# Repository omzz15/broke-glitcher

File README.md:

# Glitch Penguin 🐧
> **Glitch Penguin is a low cost all in one platform for fault injection and side channel attacks.**

There are many great glitching products out there (see [NewAE](https://www.newae.com/), [PicoGlitcher](https://fault-injection-library.readthedocs.io/en/latest/overview/)) but their cost can make the barrier to entry high especially for a large group environment such as a classroom. Glitch Penguin is a cost optimized glitching platform with a target price of only $10 a board. (We are currently at ~$16 per board using JLCPCB for board manufactuaring and assembly plus US tariffs)

## Highlights
- Powered by the [RP2040](https://www.raspberrypi.com/products/rp2040/)
- Fully open-source hardware and firmware
- Integrated analog frontend
  - 10-bit 35 MS/s ADC
  - AC coupled input range of +/-50mV
  - Bandwidth of 5 MHz
- SMA connectors for differnatial sense and glitch output
- Integrated [MSPMOG3507](https://www.ti.com/product/MSPM0G3507) target

## Overview
At the core of the board sits the RP2040 which handles

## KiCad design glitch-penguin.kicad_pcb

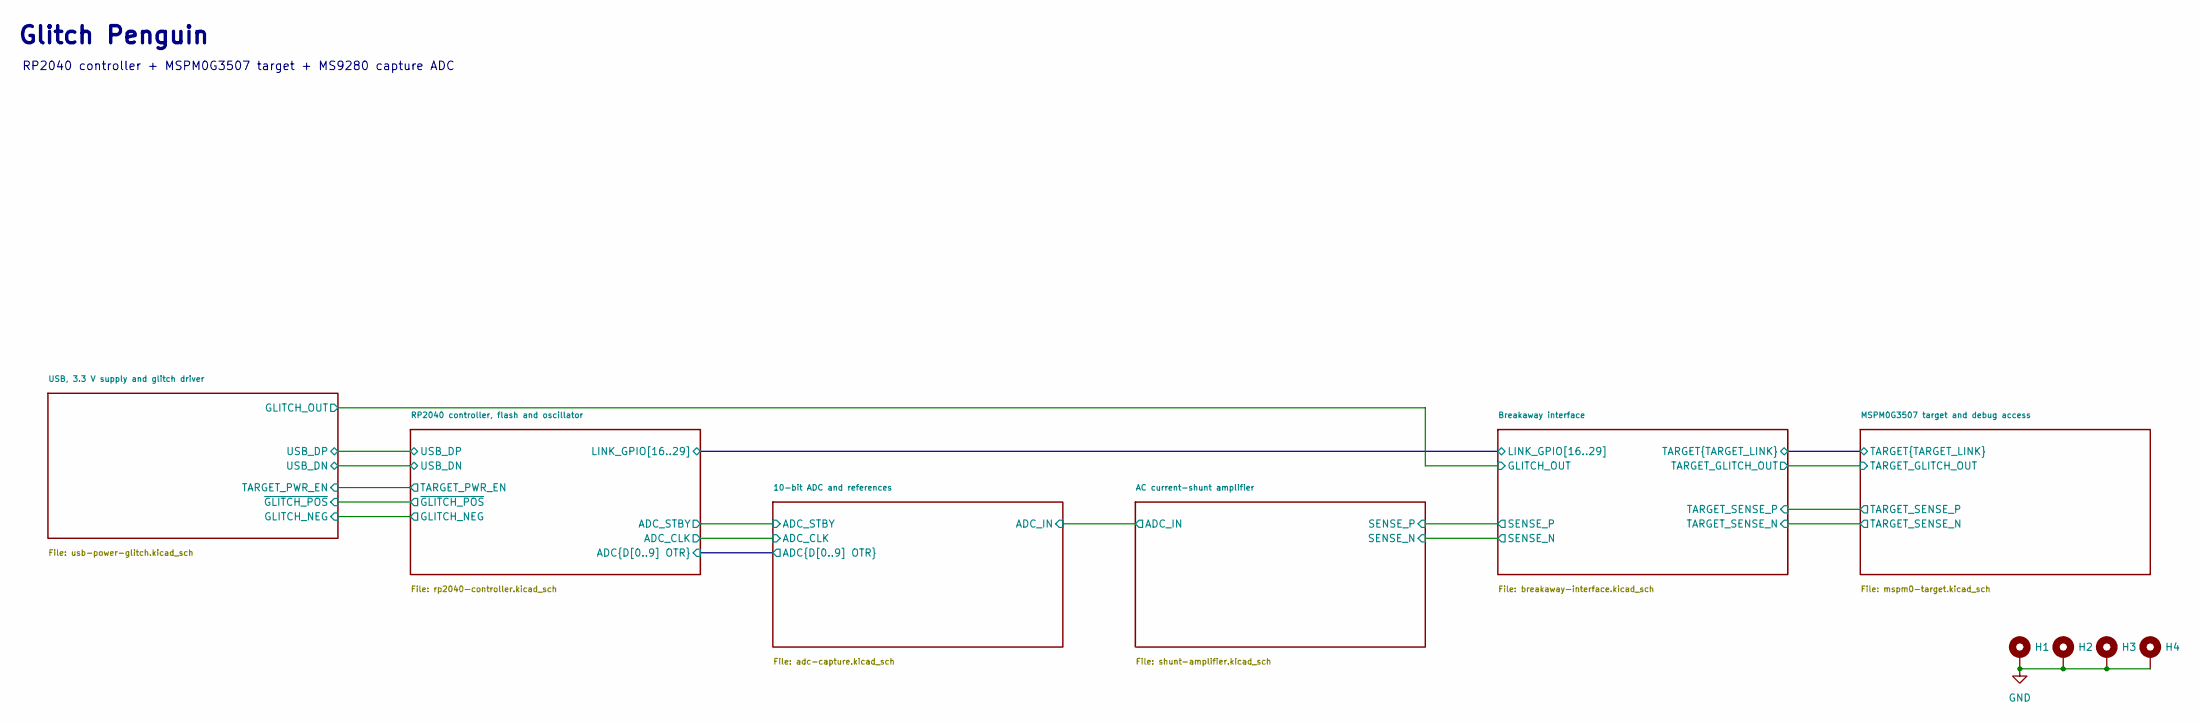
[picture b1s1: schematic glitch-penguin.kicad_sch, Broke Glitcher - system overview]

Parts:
H1, H2, H3, H4: MountingHole_Pad; MountingHole_2.2mm_M2_Pad

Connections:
GND: H1.1 (1_1), H2.1 (1_1), H3.1 (1_1), H4.1 (1_1); also elsewhere on the board

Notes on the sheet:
Glitch Penguin
RP2040 controller + MSPM0G3507 target + MS9280 capture ADC

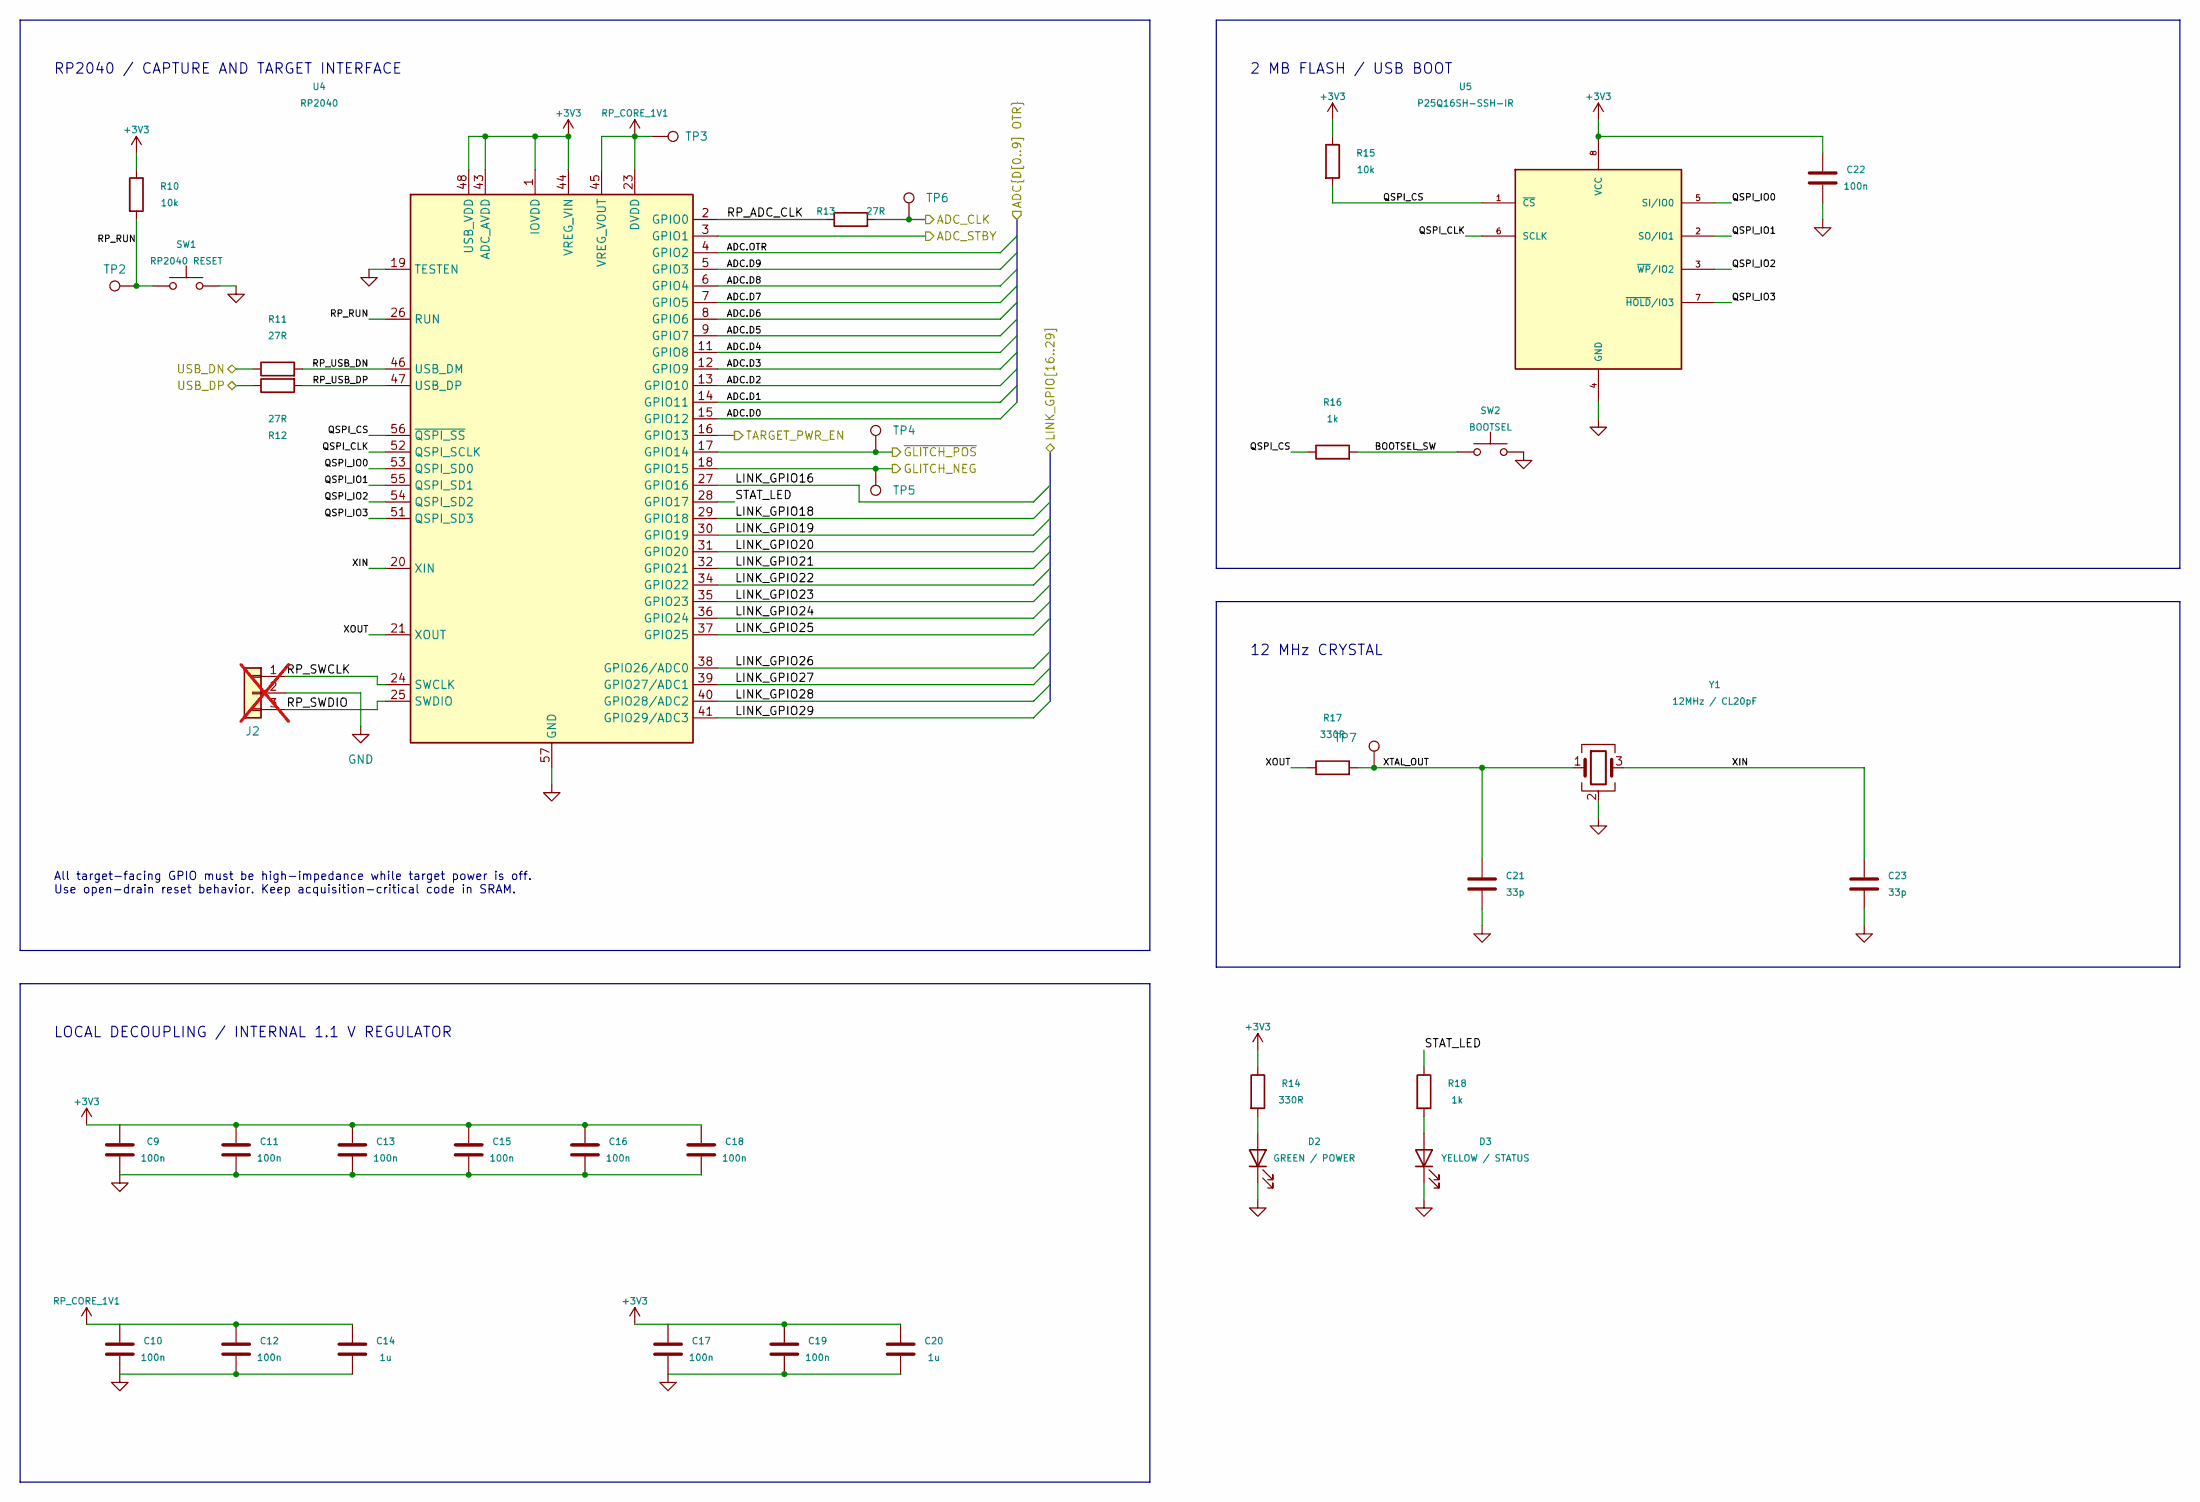
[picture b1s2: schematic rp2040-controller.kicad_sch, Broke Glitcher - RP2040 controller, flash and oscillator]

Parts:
C9, C10, C11, C12, C13, C15, C16, C17, C18, C19, C22: 100n; C_0402_1005Metric; Tolerance ±10%; Voltage Rating 16 V; MPN CL05B104KO5NNNC; LCSC Part # C1525
C14, C20: 1u; C_0603_1608Metric; MPN CL10A105KB8NNNC; LCSC Part # C15849
C21, C23: 33p; C_0402_1005Metric; Tolerance ±5%; Voltage Rating 50 V; MPN 0402CG330J500NT; LCSC Part # C1562
D2: GREEN / POWER; LED_0603_1608Metric; MPN KT-0603G; LCSC Part # C12624
D3: YELLOW / STATUS; LED_0603_1608Metric; MPN KT-0603Y; LCSC Part # C2287
J2: Conn_01x03; PinHeader_1x03_P2.54mm_Vertical; not fitted
R10, R15: 10k; R_0402_1005Metric; Tolerance ±1%; Voltage Rating 50 V; MPN 0402WGF1002TCE; LCSC Part # C25744
R11, R12, R13: 27R; R_0402_1005Metric; Tolerance ±1%; Voltage Rating 50 V; MPN 0402WGF270JTCE; LCSC Part # C25100
R14, R17: 330R; R_0402_1005Metric; Tolerance ±1%; Voltage Rating 50 V; MPN 0402WGF3300TCE; LCSC Part # C25104
R16, R18: 1k; R_0402_1005Metric; Tolerance ±1%; Voltage Rating 50 V; MPN 0402WGF1001TCE; LCSC Part # C11702
SW1: RP2040 RESET; SW_SPST_TS-1088-xR020; MPN TS-1088-AR02016; LCSC Part # C720477
SW2: BOOTSEL; SW_SPST_TS-1088-xR020; MPN TS-1088-AR02016; LCSC Part # C720477
TP2, TP3, TP4, TP5, TP6: TestPoint; TestPoint_Pad_D1.0mm
TP7: XOUT; TestPoint_Pad_D1.0mm
U4: RP2040; QFN-56-1EP_7x7mm_P0.4mm_EP3.2x3.2mm; MPN RP2040; LCSC Part # C2040
U5: P25Q16SH-SSH-IR; SOIC-8_3.9x4.9mm_P1.27mm; MPN P25Q16SH-SSH-IR; LCSC Part # C7466814
Y1: 12MHz / CL20pF; Crystal_SMD_3225-4Pin_3.2x2.5mm; MPN X322512MSB4SI; LCSC Part # C9002

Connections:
+3V3: C9.1, C11.1, C13.1, C15.1, C16.1, C17.1, C18.1, C19.1, C20.1, C22.1, R10.1, R14.1, R15.1, U4.1 (IOVDD), U4.10 (IOVDD), U4.22 (IOVDD), U4.33 (IOVDD), U4.42 (IOVDD), U4.43 (ADC_AVDD), U4.44 (VREG_VIN), U4.48 (USB_VDD), U4.49 (IOVDD), U5.8 (VCC); also elsewhere on the board
/10-bit ADC and references/ADC.D0: U4.15 (GPIO12); also elsewhere on the board
/10-bit ADC and references/ADC.D1: U4.14 (GPIO11); also elsewhere on the board
/10-bit ADC and references/ADC.D2: U4.13 (GPIO10); also elsewhere on the board
/10-bit ADC and references/ADC.D3: U4.12 (GPIO9); also elsewhere on the board
/10-bit ADC and references/ADC.D4: U4.11 (GPIO8); also elsewhere on the board
/10-bit ADC and references/ADC.D5: U4.9 (GPIO7); also elsewhere on the board
/10-bit ADC and references/ADC.D6: U4.8 (GPIO6); also elsewhere on the board
/10-bit ADC and references/ADC.D7: U4.7 (GPIO5); also elsewhere on the board
/10-bit ADC and references/ADC.D8: U4.6 (GPIO4); also elsewhere on the board
/10-bit ADC and references/ADC.D9: U4.5 (GPIO3); also elsewhere on the board
/10-bit ADC and references/ADC.OTR: U4.4 (GPIO2); also elsewhere on the board
/10-bit ADC and references/ADC_CLK: R13.2, TP6.1 (1_1); also elsewhere on the board
/10-bit ADC and references/ADC_STBY: U4.3 (GPIO1); also elsewhere on the board
/Breakaway interface/LINK_GPIO16: U4.27 (GPIO16); also elsewhere on the board
/Breakaway interface/LINK_GPIO18: U4.29 (GPIO18); also elsewhere on the board
/Breakaway interface/LINK_GPIO19: U4.30 (GPIO19); also elsewhere on the board
/Breakaway interface/LINK_GPIO20: U4.31 (GPIO20); also elsewhere on the board
/Breakaway interface/LINK_GPIO21: U4.32 (GPIO21); also elsewhere on the board
/Breakaway interface/LINK_GPIO22: U4.34 (GPIO22); also elsewhere on the board
/Breakaway interface/LINK_GPIO23: U4.35 (GPIO23); also elsewhere on the board
/Breakaway interface/LINK_GPIO24: U4.36 (GPIO24); also elsewhere on the board
/Breakaway interface/LINK_GPIO25: U4.37 (GPIO25); also elsewhere on the board
/Breakaway interface/LINK_GPIO26: U4.38 (GPIO26/ADC0); also elsewhere on the board
/Breakaway interface/LINK_GPIO27: U4.39 (GPIO27/ADC1); also elsewhere on the board
/Breakaway interface/LINK_GPIO28: U4.40 (GPIO28/ADC2); also elsewhere on the board
/Breakaway interface/LINK_GPIO29: U4.41 (GPIO29/ADC3); also elsewhere on the board
/RP2040 controller, flash and oscillator/BOOTSEL_SW: R16.2, SW2.1
/RP2040 controller, flash and oscillator/GLITCH_NEG: TP5.1 (1_1), U4.18 (GPIO15); also elsewhere on the board
/RP2040 controller, flash and oscillator/QSPI_CLK: U4.52 (QSPI_SCLK), U5.6 (SCLK)
/RP2040 controller, flash and oscillator/QSPI_CS: R15.2, R16.1, U4.56 (~QSPI_SS), U5.1 (~CS)
/RP2040 controller, flash and oscillator/QSPI_IO0: U4.53 (QSPI_SD0), U5.5 (SI/IO0)
/RP2040 controller, flash and oscillator/QSPI_IO1: U4.55 (QSPI_SD1), U5.2 (SO/IO1)
/RP2040 controller, flash and oscillator/QSPI_IO2: U4.54 (QSPI_SD2), U5.3 (~WP/IO2)
/RP2040 controller, flash and oscillator/QSPI_IO3: U4.51 (QSPI_SD3), U5.7 (~HOLD/IO3)
/RP2040 controller, flash and oscillator/RP_ADC_CLK: R13.1, U4.2 (GPIO0)
/RP2040 controller, flash and oscillator/RP_RUN: R10.2, SW1.1, TP2.1 (1_1), U4.26 (RUN)
/RP2040 controller, flash and oscillator/RP_SWCLK: J2.1, U4.24 (SWCLK)
/RP2040 controller, flash and oscillator/RP_SWDIO: J2.3, U4.25 (SWDIO)
/RP2040 controller, flash and oscillator/RP_USB_DN: R11.2, U4.46 (USB_DM)
/RP2040 controller, flash and oscillator/RP_USB_DP: R12.2, U4.47 (USB_DP)
/RP2040 controller, flash and oscillator/STAT_LED: R18.1, U4.28 (GPIO17)
/RP2040 controller, flash and oscillator/TARGET_PWR_EN: U4.16 (GPIO13); also elsewhere on the board
/RP2040 controller, flash and oscillator/USB_DN: R11.1; also elsewhere on the board
/RP2040 controller, flash and oscillator/USB_DP: R12.1; also elsewhere on the board
/RP2040 controller, flash and oscillator/XIN: C23.1, U4.20 (XIN), Y1.3
/RP2040 controller, flash and oscillator/XOUT: R17.1, U4.21 (XOUT)
/RP2040 controller, flash and oscillator/XTAL_OUT: C21.1, R17.2, TP7.1 (1_1), Y1.1
/RP2040 controller, flash and oscillator/~GLITCH_POS: TP4.1 (1_1), U4.17 (GPIO14); also elsewhere on the board
GND: C9.2, C10.2, C11.2, C12.2, C13.2, C14.2, C15.2, C16.2, C17.2, C18.2, C19.2, C20.2, C21.2, C22.2, C23.2, D2.1 (K), D3.1 (K), J2.2, SW1.2, SW2.2, U4.19 (TESTEN), U4.57 (GND), U5.4 (GND), Y1.2 (G), Y1.4 (G); also elsewhere on the board
unnamed: D2.2 (A), R14.2
unnamed: D3.2 (A), R18.2
RP_CORE_1V1: C10.1, C12.1, C14.1, TP3.1 (1_1), U4.23 (DVDD), U4.45 (VREG_VOUT), U4.50 (DVDD)

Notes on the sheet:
All target-facing GPIO must be high-impedance while target power is off. Use open-drain reset behavior. Keep acquisition-critical code in SRAM.
12 MHz CRYSTAL
LOCAL DECOUPLING / INTERNAL 1.1 V REGULATOR
RP2040 / CAPTURE AND TARGET INTERFACE
2 MB FLASH / USB BOOT

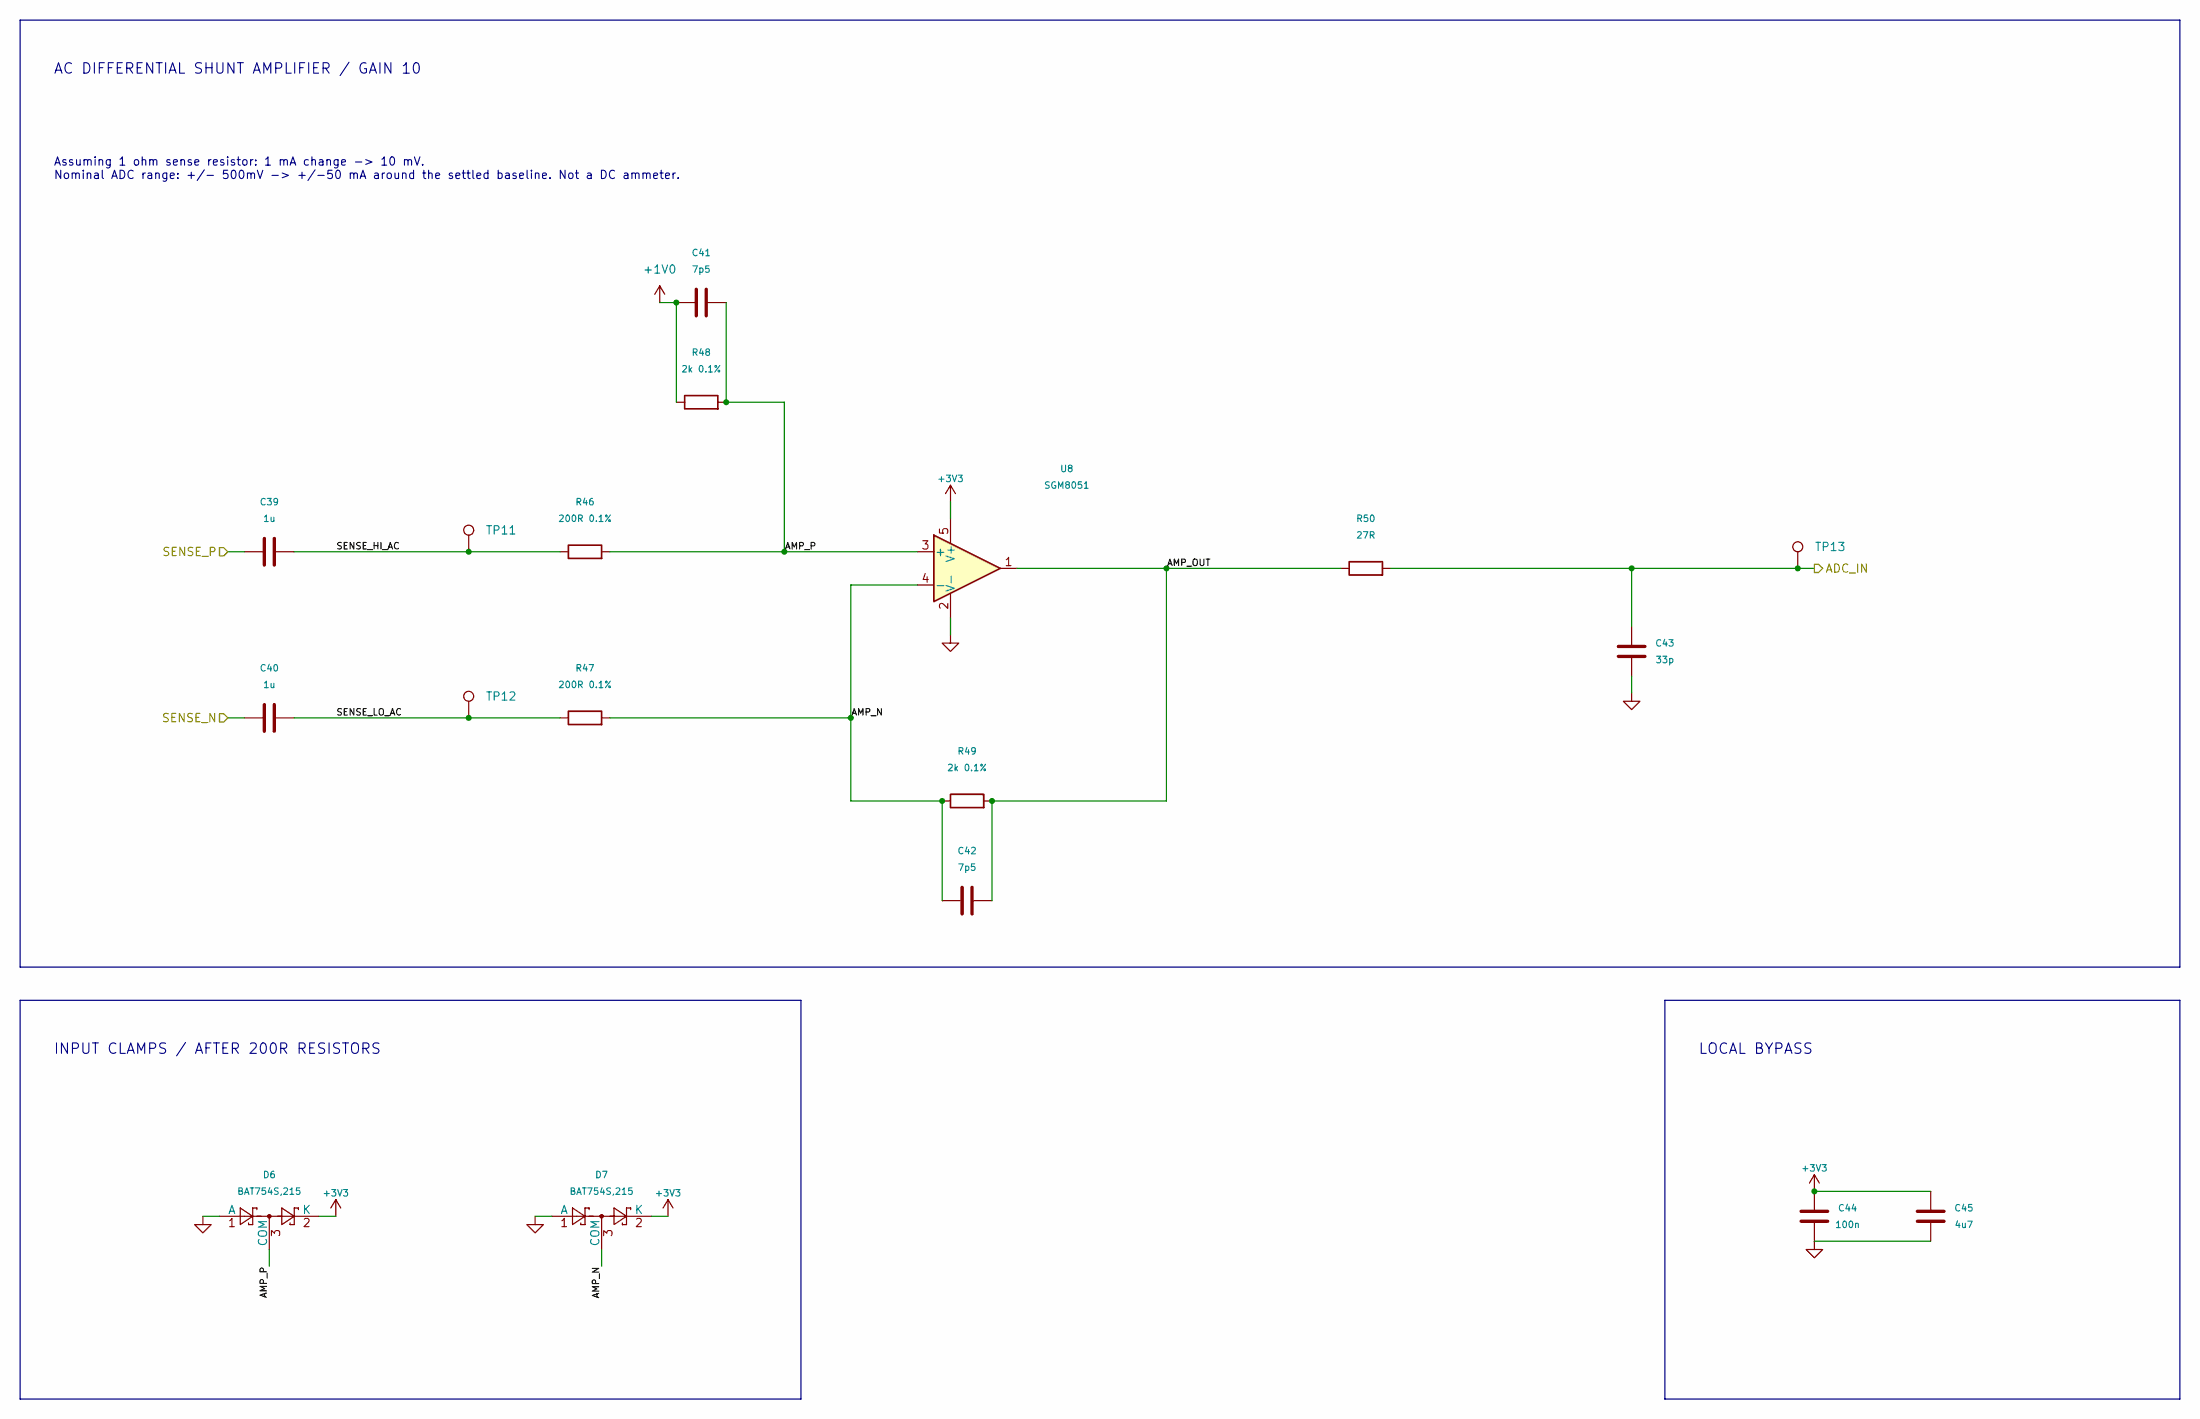
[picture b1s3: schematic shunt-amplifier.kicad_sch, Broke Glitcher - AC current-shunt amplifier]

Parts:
C39, C40: 1u; C_0603_1608Metric; MPN CL10A105KB8NNNC; LCSC Part # C15849
C41, C42: 7p5; C_0402_1005Metric; Tolerance ±0.25 pF; Voltage Rating 50 V; MPN 0402CG7R5C500NT; LCSC Part # C43514
C43: 33p; C_0402_1005Metric; Tolerance ±5%; Voltage Rating 50 V; MPN 0402CG330J500NT; LCSC Part # C1562
C44: 100n; C_0402_1005Metric; Tolerance ±10%; Voltage Rating 16 V; MPN CL05B104KO5NNNC; LCSC Part # C1525
C45: 4u7; C_0603_1608Metric; MPN CL10A475KP8NNNC; LCSC Part # C1705
D6, D7: BAT754S,215; SOT-23; MPN BAT754S,215; LCSC Part # C426771
R46, R47: 200R 0.1%; R_0603_1608Metric; MPN TC0325B2000T5F; LCSC Part # C2989022
R48, R49: 2k 0.1%; R_0402_1005Metric; Tolerance ±0.1%; Voltage Rating 50 V; MPN RT0402BRD072KL; LCSC Part # C852711
R50: 27R; R_0402_1005Metric; Tolerance ±1%; Voltage Rating 50 V; MPN 0402WGF270JTCE; LCSC Part # C25100
TP11, TP12, TP13: TestPoint; TestPoint_Pad_D1.0mm
U8: SGM8051; SOT-23-5; MPN SGM8051XN5/TR; LCSC Part # C5122371

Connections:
+1V0: C41.1, R48.1; also elsewhere on the board
+3V3: C44.1, C45.1, D6.2 (K), D7.2 (K), U8.5 (V+); also elsewhere on the board
/10-bit ADC and references/ADC_IN: C43.1, R50.2, TP13.1 (1_1); also elsewhere on the board
/AC current-shunt amplifier/AMP_N: C42.1, D7.3 (COM), R47.2, R49.1, U8.4 (-)
/AC current-shunt amplifier/AMP_OUT: C42.2, R49.2, R50.1, U8.1
/AC current-shunt amplifier/AMP_P: C41.2, D6.3 (COM), R46.2, R48.2, U8.3 (+)
/AC current-shunt amplifier/SENSE_HI_AC: C39.2, R46.1, TP11.1 (1_1)
/AC current-shunt amplifier/SENSE_LO_AC: C40.2, R47.1, TP12.1 (1_1)
/AC current-shunt amplifier/SENSE_N: C40.1; also elsewhere on the board
/AC current-shunt amplifier/SENSE_P: C39.1; also elsewhere on the board
GND: C43.2, C44.2, C45.2, D6.1 (A), D7.1 (A), U8.2 (V-); also elsewhere on the board

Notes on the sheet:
AC DIFFERENTIAL SHUNT AMPLIFIER / GAIN 10
Assuming 1 ohm sense resistor: 1 mA change -> 10 mV. Nominal ADC range: +/- 500mV -> +/-50 mA around the settled baseline. Not a DC ammeter.
LOCAL BYPASS
INPUT CLAMPS / AFTER 200R RESISTORS

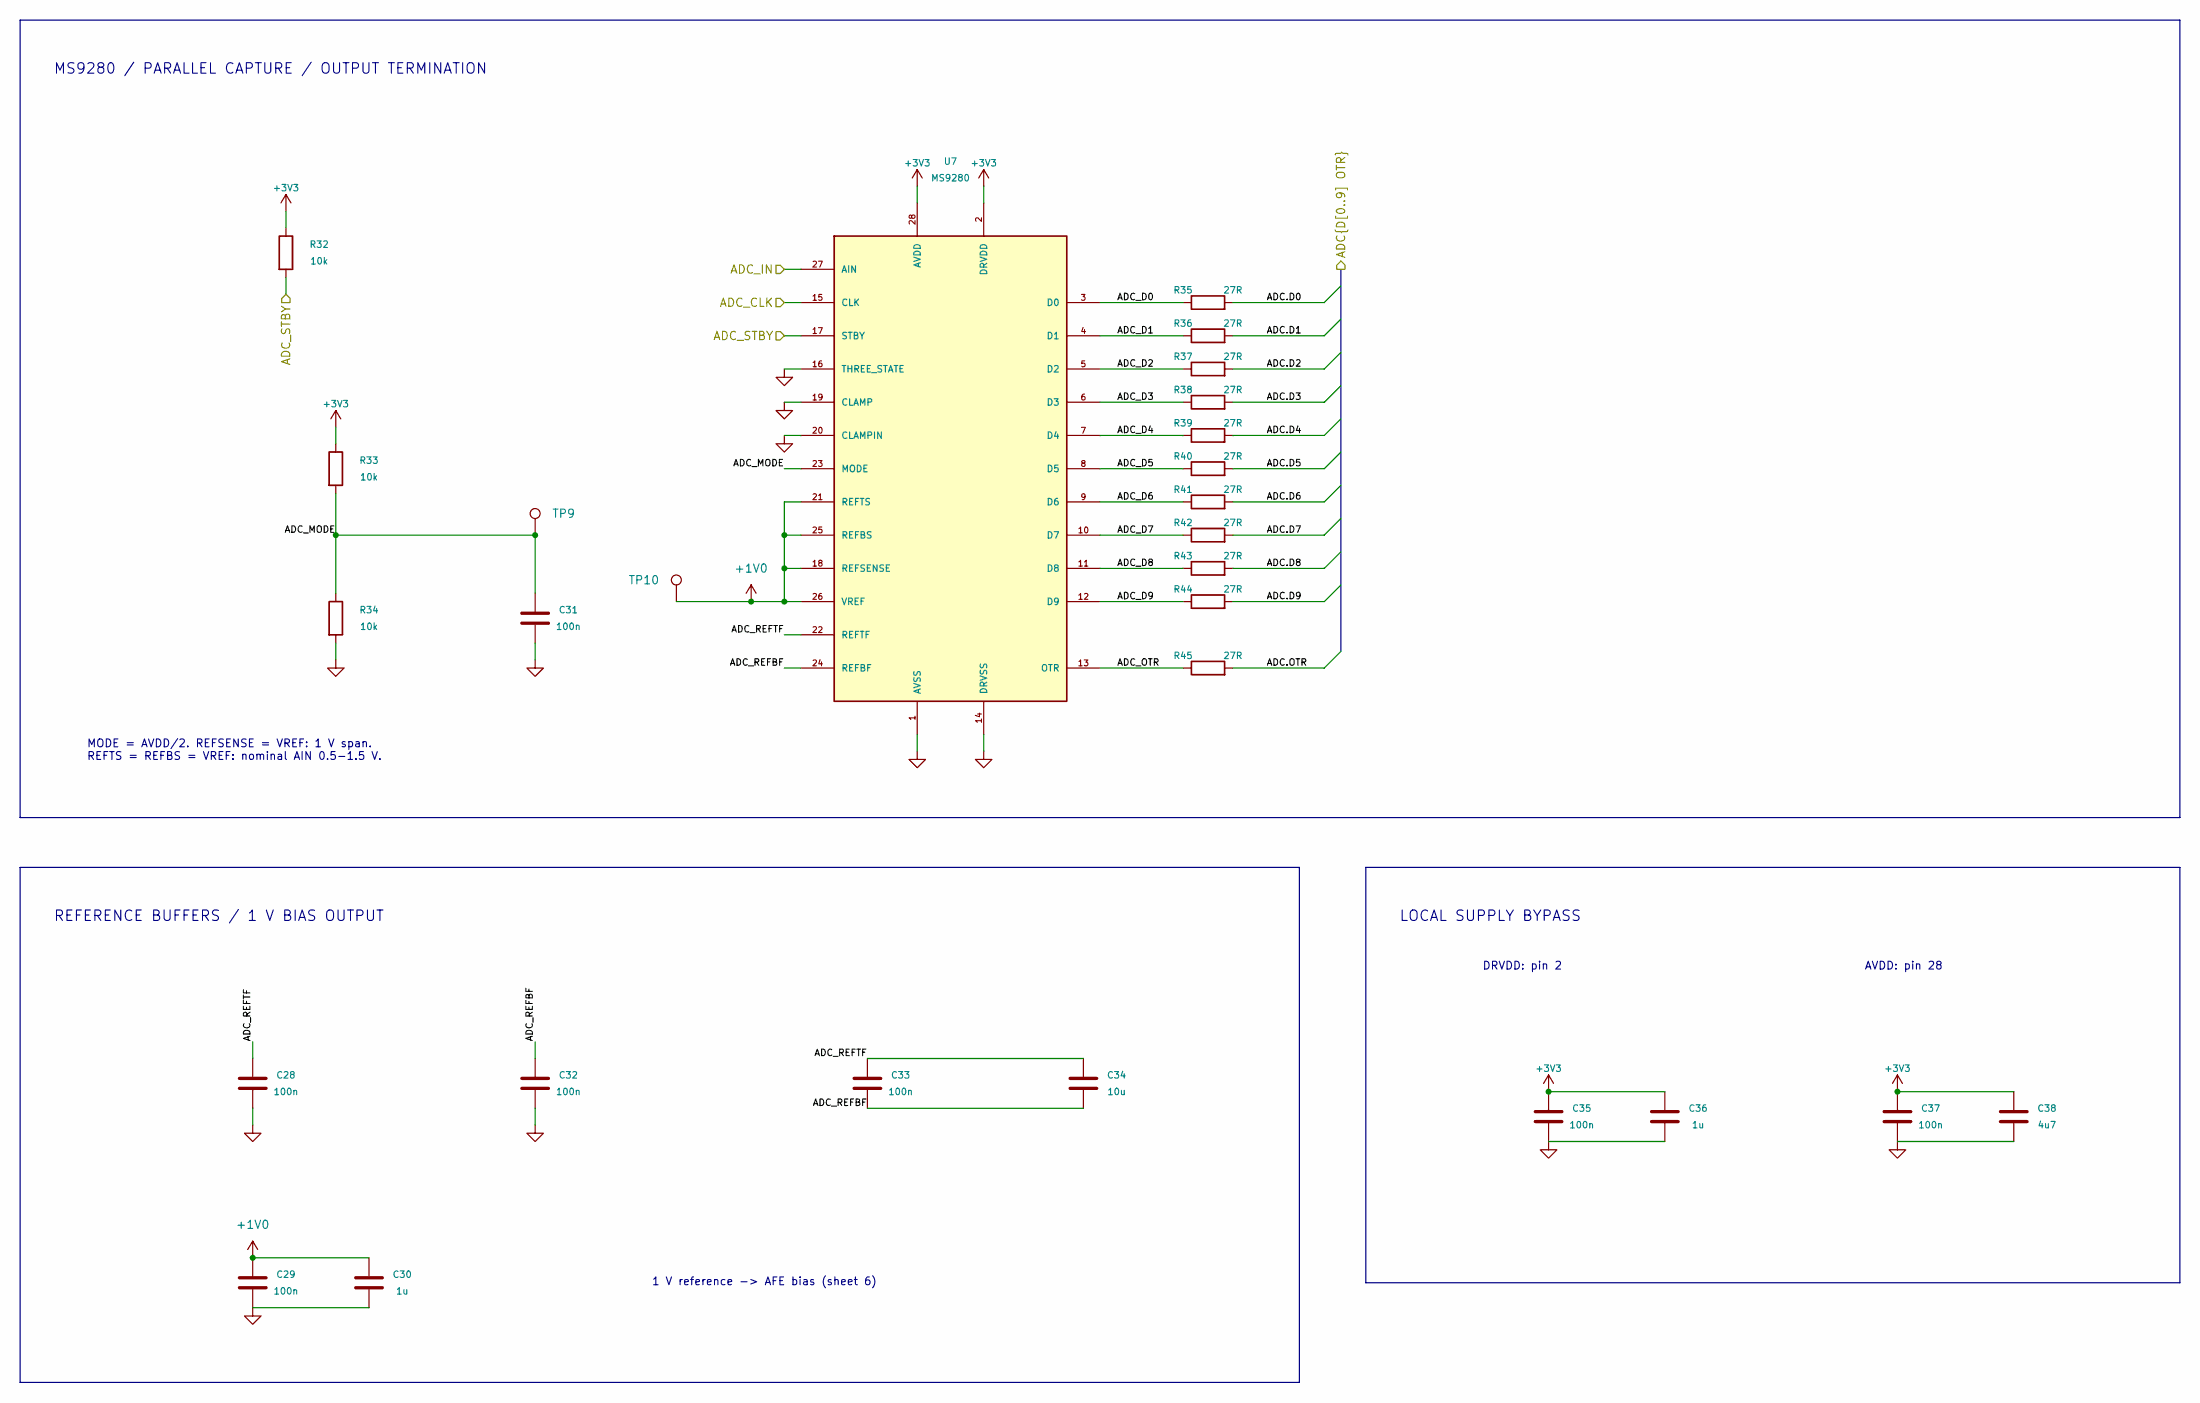
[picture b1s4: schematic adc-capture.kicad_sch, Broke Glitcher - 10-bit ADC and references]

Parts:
C28, C29, C31, C32, C33, C35, C37: 100n; C_0402_1005Metric; Tolerance ±10%; Voltage Rating 16 V; MPN CL05B104KO5NNNC; LCSC Part # C1525
C30, C36: 1u; C_0603_1608Metric; MPN CL10A105KB8NNNC; LCSC Part # C15849
C34: 10u; C_0805_2012Metric; MPN CL21A106KAYNNNE; LCSC Part # C15850
C38: 4u7; C_0603_1608Metric; MPN CL10A475KP8NNNC; LCSC Part # C1705
R32, R33, R34: 10k; R_0402_1005Metric; Tolerance ±1%; Voltage Rating 50 V; MPN 0402WGF1002TCE; LCSC Part # C25744
R35, R36, R37, R38, R39, R40, R41, R42, R43, R44, R45: 27R; R_0402_1005Metric; Tolerance ±1%; Voltage Rating 50 V; MPN 0402WGF270JTCE; LCSC Part # C25100
TP9, TP10: TestPoint; TestPoint_Pad_D1.0mm
U7: MS9280; SSOP-28_5.3x10.2mm_P0.65mm; MPN MS9280; LCSC Part # C1509021

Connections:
+1V0: C29.1, C30.1, TP10.1 (1_1), U7.18 (REFSENSE), U7.21 (REFTS), U7.25 (REFBS), U7.26 (VREF); also elsewhere on the board
+3V3: C35.1, C36.1, C37.1, C38.1, R32.1, R33.1, U7.2 (DRVDD), U7.28 (AVDD); also elsewhere on the board
/10-bit ADC and references/ADC.D0: R35.2; also elsewhere on the board
/10-bit ADC and references/ADC.D1: R36.2; also elsewhere on the board
/10-bit ADC and references/ADC.D2: R37.2; also elsewhere on the board
/10-bit ADC and references/ADC.D3: R38.2; also elsewhere on the board
/10-bit ADC and references/ADC.D4: R39.2; also elsewhere on the board
/10-bit ADC and references/ADC.D5: R40.2; also elsewhere on the board
/10-bit ADC and references/ADC.D6: R41.2; also elsewhere on the board
/10-bit ADC and references/ADC.D7: R42.2; also elsewhere on the board
/10-bit ADC and references/ADC.D8: R43.2; also elsewhere on the board
/10-bit ADC and references/ADC.D9: R44.2; also elsewhere on the board
/10-bit ADC and references/ADC.OTR: R45.2; also elsewhere on the board
/10-bit ADC and references/ADC_CLK: U7.15 (CLK); also elsewhere on the board
/10-bit ADC and references/ADC_D0: R35.1, U7.3 (D0)
/10-bit ADC and references/ADC_D1: R36.1, U7.4 (D1)
/10-bit ADC and references/ADC_D2: R37.1, U7.5 (D2)
/10-bit ADC and references/ADC_D3: R38.1, U7.6 (D3)
/10-bit ADC and references/ADC_D4: R39.1, U7.7 (D4)
/10-bit ADC and references/ADC_D5: R40.1, U7.8 (D5)
/10-bit ADC and references/ADC_D6: R41.1, U7.9 (D6)
/10-bit ADC and references/ADC_D7: R42.1, U7.10 (D7)
/10-bit ADC and references/ADC_D8: R43.1, U7.11 (D8)
/10-bit ADC and references/ADC_D9: R44.1, U7.12 (D9)
/10-bit ADC and references/ADC_IN: U7.27 (AIN); also elsewhere on the board
/10-bit ADC and references/ADC_MODE: C31.1, R33.2, R34.1, TP9.1 (1_1), U7.23 (MODE)
/10-bit ADC and references/ADC_OTR: R45.1, U7.13 (OTR)
/10-bit ADC and references/ADC_REFBF: C32.1, C33.2, C34.2, U7.24 (REFBF)
/10-bit ADC and references/ADC_REFTF: C28.1, C33.1, C34.1, U7.22 (REFTF)
/10-bit ADC and references/ADC_STBY: R32.2, U7.17 (STBY); also elsewhere on the board
GND: C28.2, C29.2, C30.2, C31.2, C32.2, C35.2, C36.2, C37.2, C38.2, R34.2, U7.1 (AVSS), U7.14 (DRVSS), U7.16 (THREE_STATE), U7.19 (CLAMP), U7.20 (CLAMPIN); also elsewhere on the board

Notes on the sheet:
REFERENCE BUFFERS / 1 V BIAS OUTPUT
MODE = AVDD/2. REFSENSE = VREF: 1 V span. REFTS = REFBS = VREF: nominal AIN 0.5-1.5 V.
1 V reference -> AFE bias (sheet 6)
DRVDD: pin 2
LOCAL SUPPLY BYPASS
AVDD: pin 28
MS9280 / PARALLEL CAPTURE / OUTPUT TERMINATION
